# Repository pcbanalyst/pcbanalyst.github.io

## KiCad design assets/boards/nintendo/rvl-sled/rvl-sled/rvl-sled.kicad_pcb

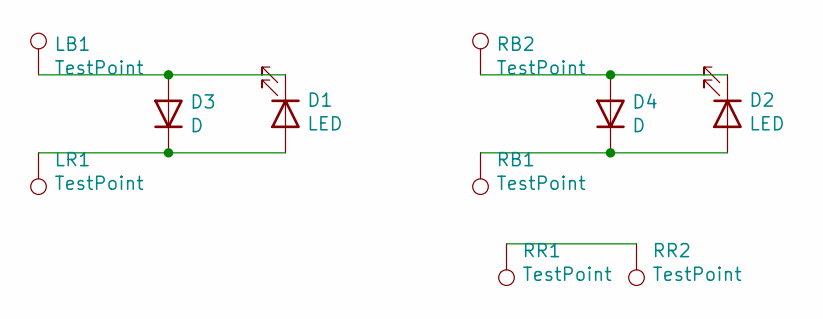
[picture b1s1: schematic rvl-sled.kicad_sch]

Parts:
D1, D2: LED; LED_0603_1608Metric
D3, D4: D; D_0805_2012Metric
LB1: TestPoint; TestPoint_Pad_3.0x3.0mm
LR1: TestPoint; TestPoint_Pad_3.0x3.0mm
RB1, RB2: TestPoint; TestPoint_Pad_3.0x3.0mm
RR1, RR2: TestPoint; TestPoint_Pad_3.0x3.0mm

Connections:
unnamed: D1.1 (K), D3.2 (A), LB1.1
unnamed: D1.2 (A), D3.1 (K), LR1.1
unnamed: D2.1 (K), D4.2 (A), RB2.1
unnamed: D2.2 (A), D4.1 (K), RB1.1
unnamed: RR1.1, RR2.1

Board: 2 copper layers, 10 parts (6 on the bottom side), 5 nets, no tracks yet.

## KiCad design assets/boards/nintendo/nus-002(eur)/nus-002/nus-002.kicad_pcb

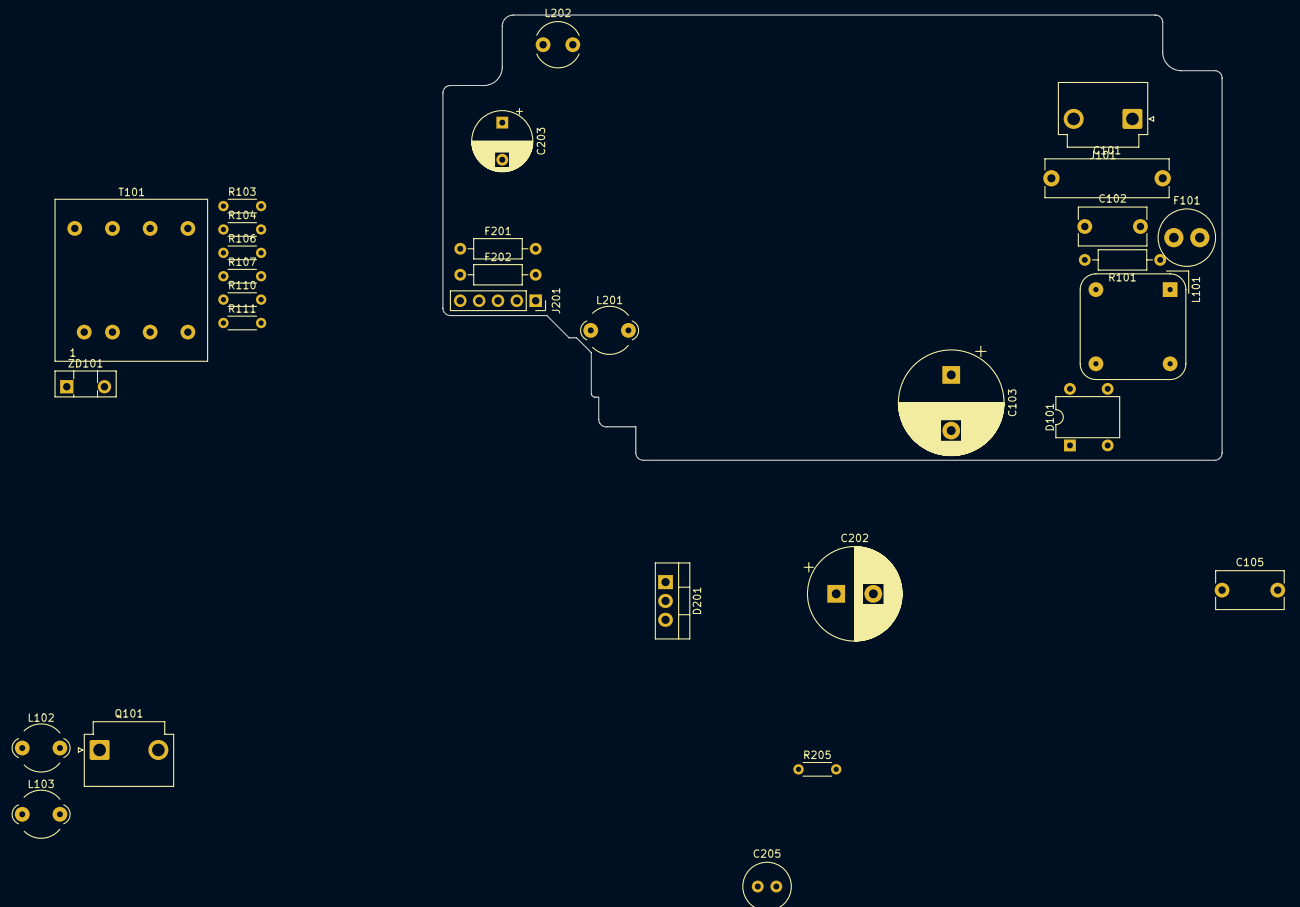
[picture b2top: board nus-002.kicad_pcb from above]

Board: 2 copper layers, 105.0 x 60.0 mm, 30 parts (0 on the bottom side), 23 nets, no tracks yet.

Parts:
C101: C; C_Rect_L16.5mm_W5.0mm_P15.00mm_MKT
C102: C; C_Disc_D9.0mm_W5.0mm_P7.50mm
C103: 47uF 400V; CP_Radial_D14.0mm_P7.50mm
C105: KH472M; C_Disc_D9.0mm_W5.0mm_P7.50mm
C202: 680uF 35V; CP_Radial_D12.5mm_P5.00mm
C203: 560uF 25V; CP_Radial_D8.0mm_P5.00mm
C205: 330uF 10V; C_Radial_D6.3mm_H5.0mm_P2.50mm
D101: S1WB; Diode_Bridge_DIP-4_W7.62mm_P5.08mm
D201: MA10799; TO-220-3_Vertical
F101: Fuse; L_Radial_D7.5mm_P3.50mm_Fastron_07P
F201, F202: Fuse; R_Axial_DIN0207_L6.3mm_D2.5mm_P10.16mm_Horizontal
J101: Conn_WallPlug; JST_VH_B2P3-VH_1x02_P7.92mm_Vertical
J201: Conn_01x05; PinSocket_1x05_P2.54mm_Vertical
L101: EMI_Filter_CommonMode; Choke_Schaffner_RN102-04-14.0x14.0mm
L102, L103, L201: Ferrite_Bead; LairdTech_28C0236-0JW-10
L202: L_Core_Ferrite; L_Radial_D6.0mm_P4.00mm
Q101: Q_NMOS_GDS; JST_VH_B2P3-VH_1x02_P7.92mm_Vertical
R101: 3.1k; R_Axial_DIN0207_L6.3mm_D2.5mm_P10.16mm_Horizontal
R103, R104, R106, R107, R110, R111: R; R_Axial_DIN0204_L3.6mm_D1.6mm_P5.08mm_Horizontal
R205: 3.1k; R_Axial_DIN0204_L3.6mm_D1.6mm_P5.08mm_Horizontal
T101: BM116A; Transformer_Coilcraft_Q4434-B_Rhombus-T1311
ZD101: D_Zener; TO-126-2_Vertical

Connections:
GND: C202.2, C203.2, C205.2, J201.1, J201.2, R205.2
unnamed: C101.2, C102.2, F101.1, L101.1, R101.1
unnamed: C202.1, L202.2
unnamed: C205.1, F201.2, L202.1, R205.1
unnamed: C103.2, D101.1 (+)
unnamed: C103.1, D101.4 (-), R103.1, T101.4
unnamed: D101.2, L101.2
unnamed: D101.3, L101.4
unnamed: L102.2, T101.3
unnamed: D201.1 (A), D201.3 (A)
unnamed: C203.1, D201.2 (K), L201.2
unnamed: F202.2, L201.1
unnamed: C101.1, C102.1, J101.2 (AC_N), L101.3, R101.2
unnamed: F101.2, J101.1 (AC_P)
unnamed: F201.1, J201.3, J201.4
unnamed: F202.1, J201.5
unnamed: L103.2, R104.1, T101.2
unnamed: L102.1, Q101.2 (D)
unnamed: R103.2, R106.1
unnamed: R106.2, R110.1
unnamed: R110.2, R111.1
unnamed: R111.2, ZD101.1 (K)
SUB3: C105.1, T101.1, ZD101.2 (A)

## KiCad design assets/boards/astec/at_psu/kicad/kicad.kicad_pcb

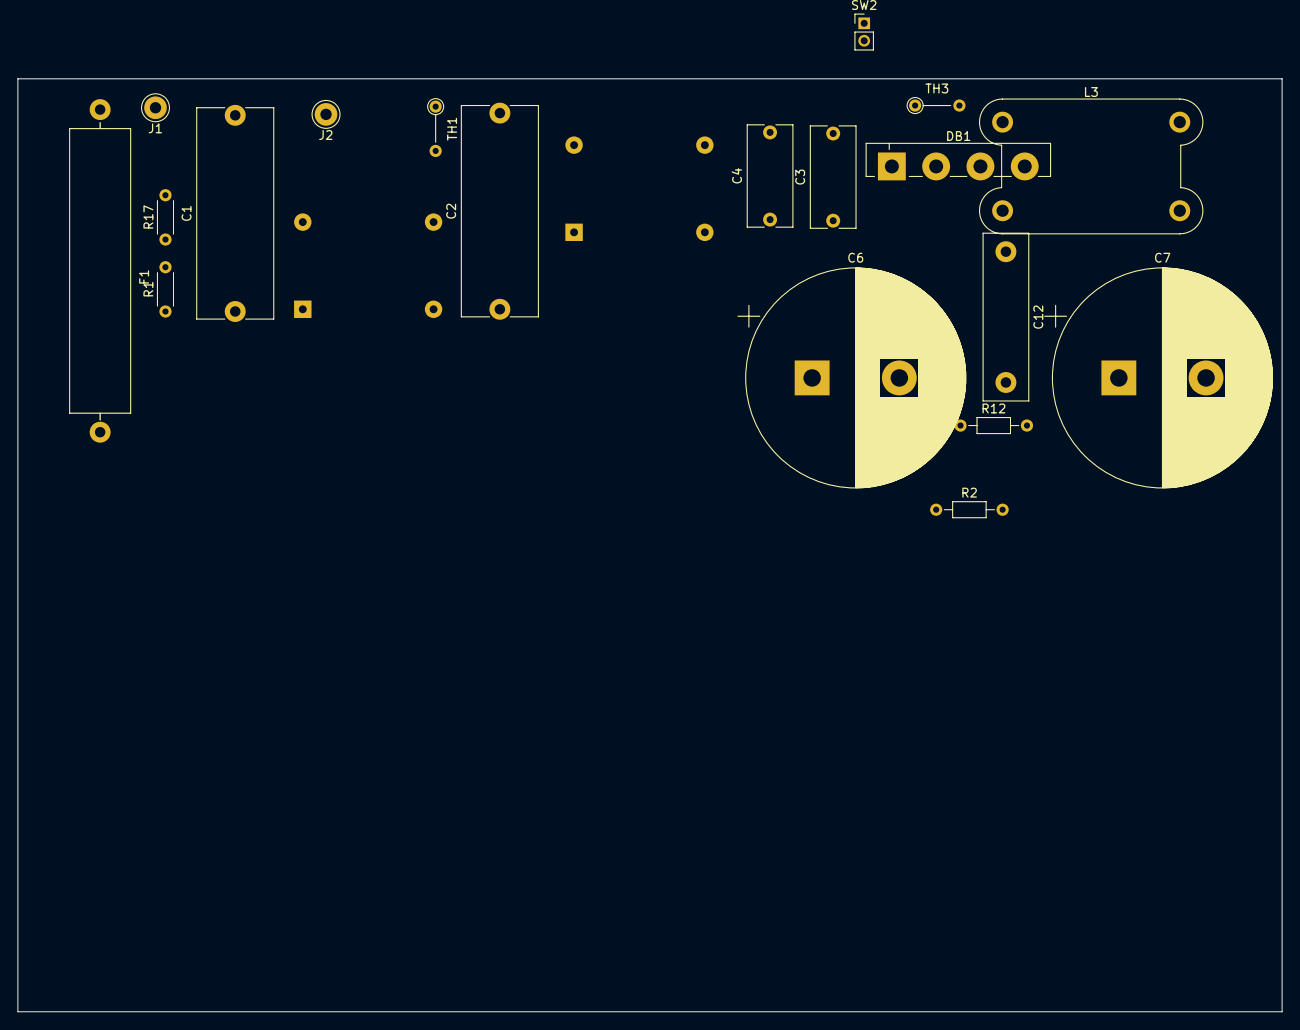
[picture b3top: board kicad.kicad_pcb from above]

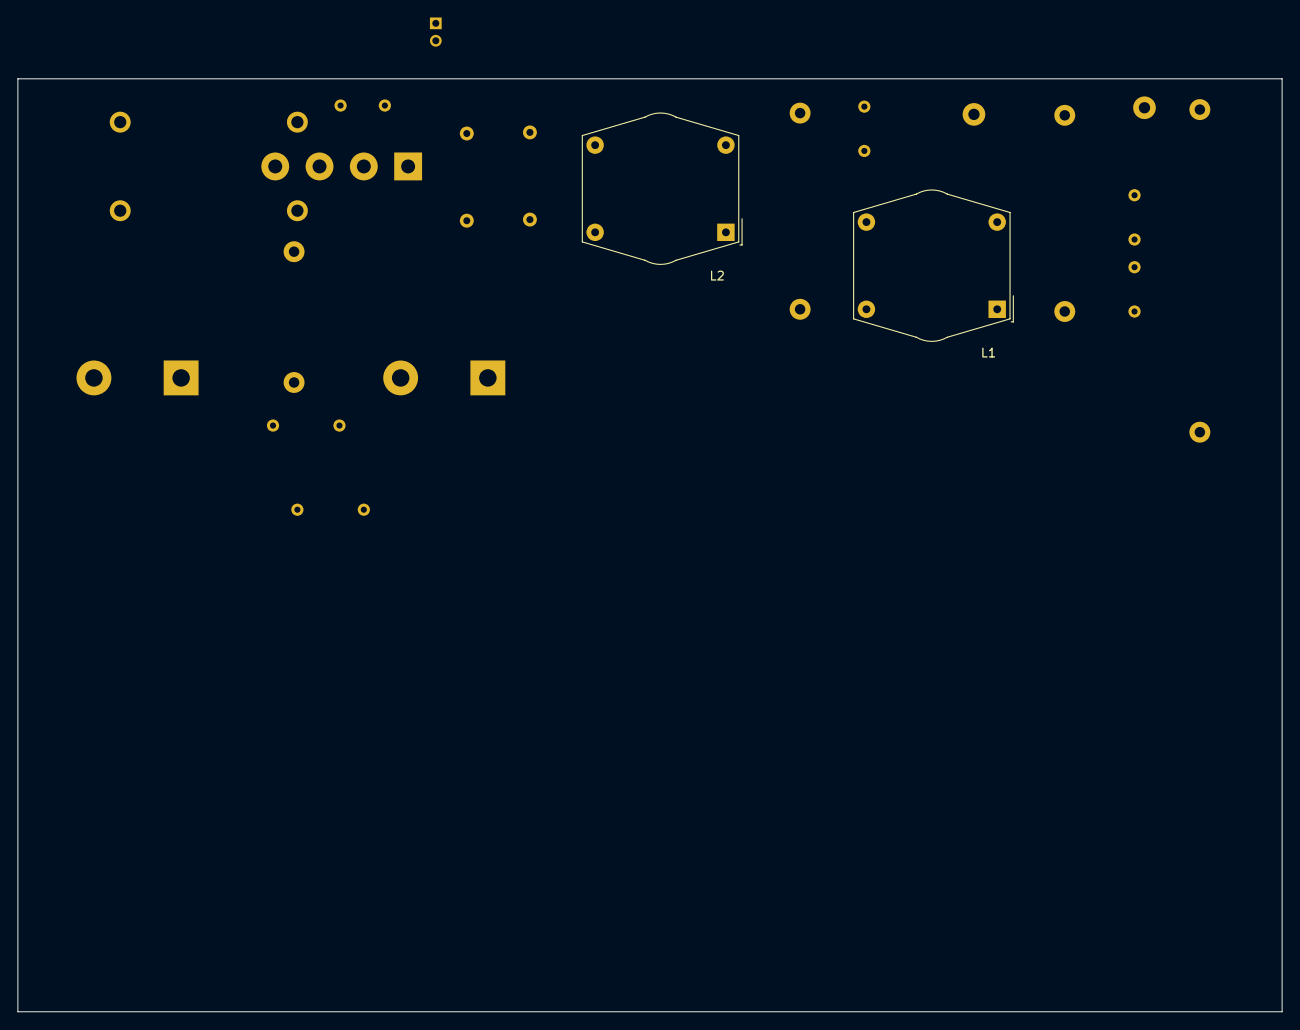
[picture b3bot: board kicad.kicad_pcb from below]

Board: 2 copper layers, 145.0 x 107.0 mm, 21 parts (2 on the bottom side), 16 nets, no tracks yet.

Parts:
C1, C2: C; C_Rect_L24.0mm_W8.6mm_P22.50mm_MKT
C3, C4: C; C_Rect_L11.5mm_W5.0mm_P10.00mm_MKT
C6, C7: CP; CP_Radial_D25.0mm_P10.00mm_SnapIn
C12: C; C_Rect_L19.0mm_W5.0mm_P15.00mm_MKS4
DB1: B40R; Diode_Bridge_Vishay_GBL
F1: Fuse; Fuse_SunFuse-6HP
J1, J2: Conn_01x01; Pin_D1.3mm_L11.0mm
L1, L2: L_Coupled; Choke_Schaffner_RN112-04-17.7x17.1mm
L3: L_Coupled_Small; L_Mount_Lodestone_VTM120
R1, R17: R; R_Axial_DIN0204_L3.6mm_D1.6mm_P5.08mm_Horizontal
R2, R12: R; R_Axial_DIN0204_L3.6mm_D1.6mm_P7.62mm_Horizontal
SW2: SW_SPST; PinHeader_1x02_P2.00mm_Vertical
TH1, TH3: Thermistor; R_Axial_DIN0204_L3.6mm_D1.6mm_P5.08mm_Vertical

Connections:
Earth: C3.2, C4.1
unnamed: C1.1, F1.1, L1.1, R1.1
unnamed: C1.2, J2.1, L1.3, R17.2
unnamed: C2.1, L1.2, L2.1
unnamed: C2.2, L2.3, TH1.1
unnamed: C4.2, L2.4, SW2.1, TH3.1
unnamed: C6.1, DB1.1, R2.1
unnamed: C6.2, C7.1, L3.4, R2.2
unnamed: C7.2, DB1.3, L3.2
unnamed: C3.1, C12.1, DB1.4, L2.2
unnamed: C12.2, R12.1
unnamed: DB1.2, TH3.2
unnamed: F1.2, J1.1
unnamed: L1.4, TH1.2
unnamed: L3.1, SW2.2
unnamed: R1.2, R17.1

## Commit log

2021-01-18 Create CNAME
2021-01-18 skeleton
2021-01-18 upload first 4 posts
2021-01-18 update jekyll
2021-01-18 add unfinished boards
2021-09-30 add karaoke
2023-11-27 add gigaset
2023-12-09 denmok
2023-12-13 rest
2023-12-13 layout
2024-10-07 add errors
2026-02-21 serial
    Updated text for clarity and corrected capitalization.
2026-05-29 maskrom
    Updated the ROMs section to specify Mask ROMs and added a new entry.
